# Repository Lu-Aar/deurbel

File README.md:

# deurbel
Making an ordinairy doorbell smart by having a notification through discord and ringing a klikaanklikuit chime.

When the doorbell is pressed there are three notifications:
- A mechanical chime
- A KlikAanKlikUit chime
- A Discord notification

There are also two extra inputs:
- A test button: Added to to test the doorbell functionality
- A mute switch: This can enable/disable the chimes

This project is fully designed in RUST no_std and it's designed to be used with a ESP32-WROOM-32.

## ToDo after clone
When this repo is cloned there is one step which has to be done before the code can be used.
Inside the bin folder the following file needs to be created:
global/mod.rs

This file should contain the following items:
``` rust
pub const WIFI_SSID: &str = "THE_SSID_TO_CONNECT_TO";
pub const WIFI_PASSWORD: &str = "THE_PASSWORD_OF_THE_SSID";
pub const DISCORD_WEBHOOK_URL: &str = "THE_URL_OF_THE_DISCORD_WEBHOOK_TO_USE";
pub const DISCORD_TTS: &str = false; // Set to true when to use Text To Speech
```

## PCB
The PCB was created in KiCad. It's a free opensource program for creating schematics and PCB's.
https://www.kicad.org/

## How to flash
. export-esp.sh

cargo build && cargo run

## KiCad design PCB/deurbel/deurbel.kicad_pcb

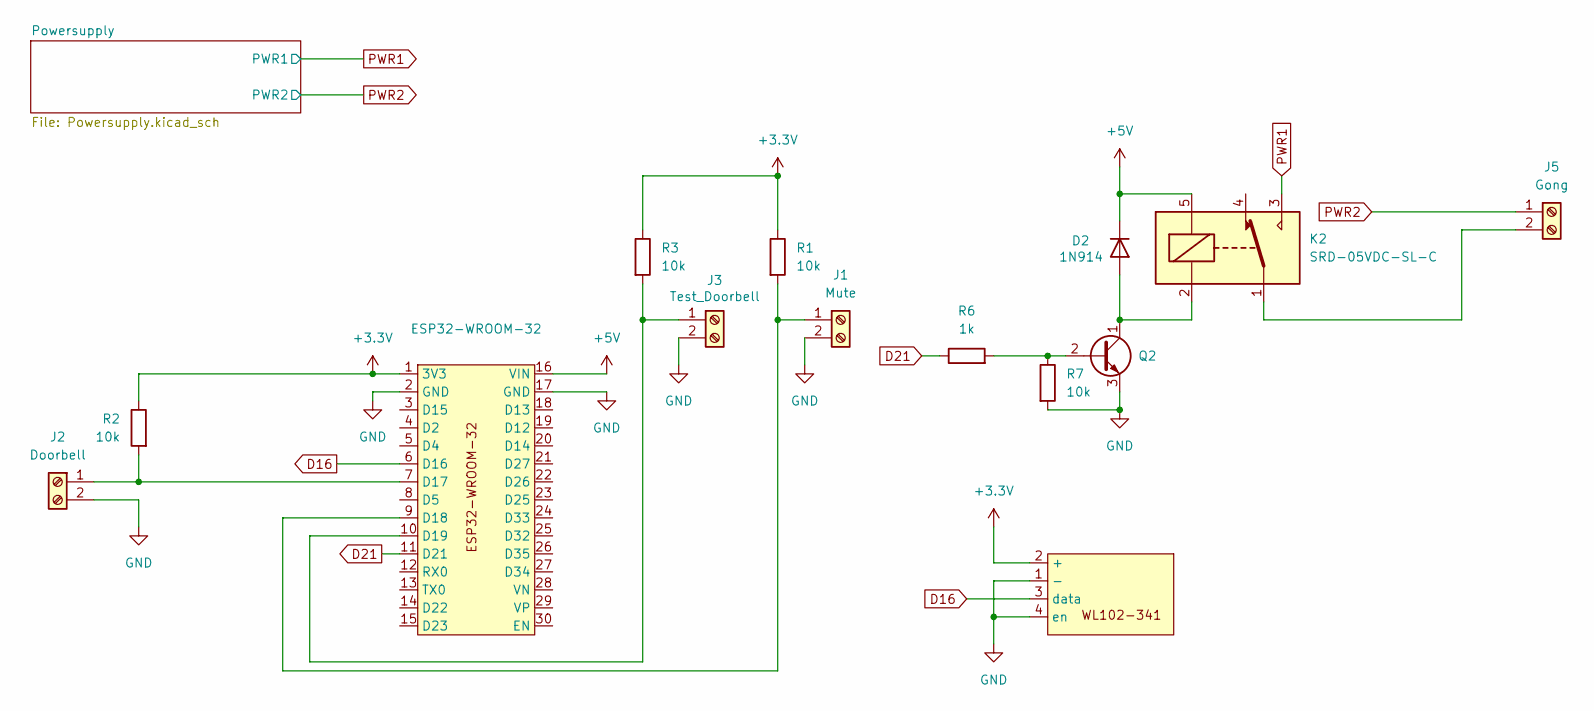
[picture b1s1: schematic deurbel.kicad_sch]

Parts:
D2: 1N914; D_DO-35_SOD27_P7.62mm_Horizontal
ESP32-WROOM-32: ESP32-WROOM-32
J1: Mute; TerminalBlock_Xinya_XY308-2.54-2P_1x02_P2.54mm_Horizontal
J2: Doorbell; TerminalBlock_Xinya_XY308-2.54-2P_1x02_P2.54mm_Horizontal
J3: Test_Doorbell; TerminalBlock_Xinya_XY308-2.54-2P_1x02_P2.54mm_Horizontal
J5: Gong; TerminalBlock_Xinya_XY308-2.54-2P_1x02_P2.54mm_Horizontal
K2: SRD-05VDC-SL-C; Relay_SPDT_SANYOU_SRD_Series_Form_C
Q2: BC338; TO-92_Inline
R1, R2, R3, R7: 10k; R_Axial_DIN0204_L3.6mm_D1.6mm_P5.08mm_Horizontal
R6: 1k; R_Axial_DIN0204_L3.6mm_D1.6mm_P5.08mm_Horizontal
WL102-1: WL102-341

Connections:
+3.3V: ESP32-WROOM-32.1 (3V3), R1.1, R2.1, R3.1, WL102-1.2 (+)
+5V: D2.1 (K), ESP32-WROOM-32.16 (VIN), K2.5; also elsewhere on the board
D16: ESP32-WROOM-32.6 (D16), WL102-1.3 (data)
D21: ESP32-WROOM-32.11 (D21), R6.1
GND: ESP32-WROOM-32.2 (GND), ESP32-WROOM-32.17 (GND), J1.2, J2.2, J3.2, Q2.3 (E), R7.2, WL102-1.1 (-), WL102-1.4 (en); also elsewhere on the board
unnamed: D2.2 (A), K2.2, Q2.1 (C)
unnamed: ESP32-WROOM-32.7 (D17), J2.1, R2.2
unnamed: ESP32-WROOM-32.9 (D18), J1.1, R1.2
unnamed: ESP32-WROOM-32.10 (D19), J3.1, R3.2
unnamed: J5.2, K2.1
unnamed: Q2.2 (B), R6.2, R7.1
PWR1: K2.3; also elsewhere on the board
PWR2: J5.1; also elsewhere on the board

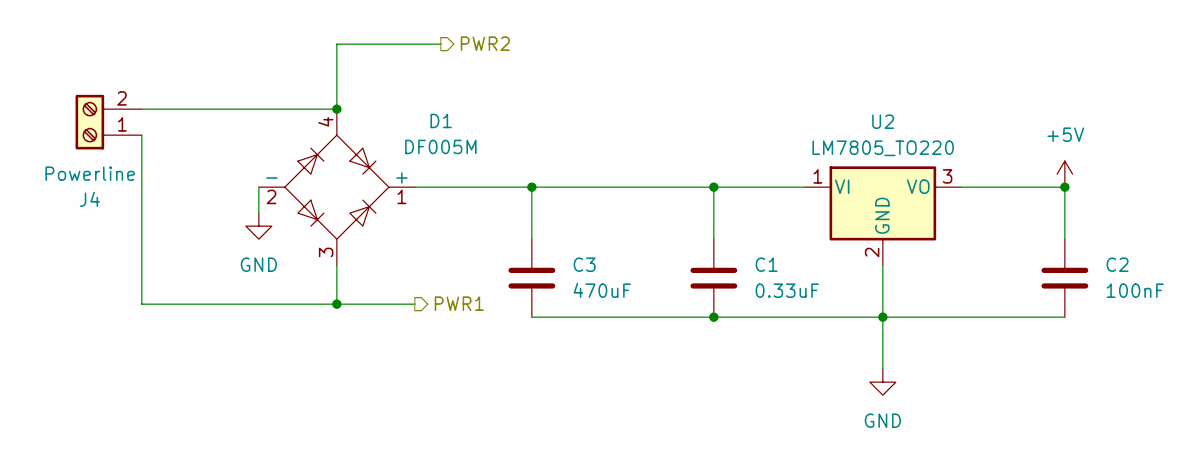
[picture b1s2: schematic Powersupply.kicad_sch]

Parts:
C1: 0.33uF; C_Disc_D4.3mm_W1.9mm_P5.00mm
C2: 100nF; C_Disc_D4.3mm_W1.9mm_P5.00mm
C3: 470uF; CP_Radial_D10.0mm_P5.00mm
D1: DF005M; Diode_Bridge_DIP-4_W7.62mm_P5.08mm
J4: Powerline; TerminalBlock_Xinya_XY308-2.54-2P_1x02_P2.54mm_Horizontal
U2: LM7805_TO220; TO-220-3_Vertical

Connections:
+5V: C2.1, U2.3 (VO); also elsewhere on the board
GND: C1.2, C2.2, C3.2, D1.2 (-), U2.2 (GND); also elsewhere on the board
unnamed: C1.1, C3.1, D1.1 (+), U2.1 (VI)
PWR1: D1.3, J4.1; also elsewhere on the board
PWR2: D1.4, J4.2; also elsewhere on the board

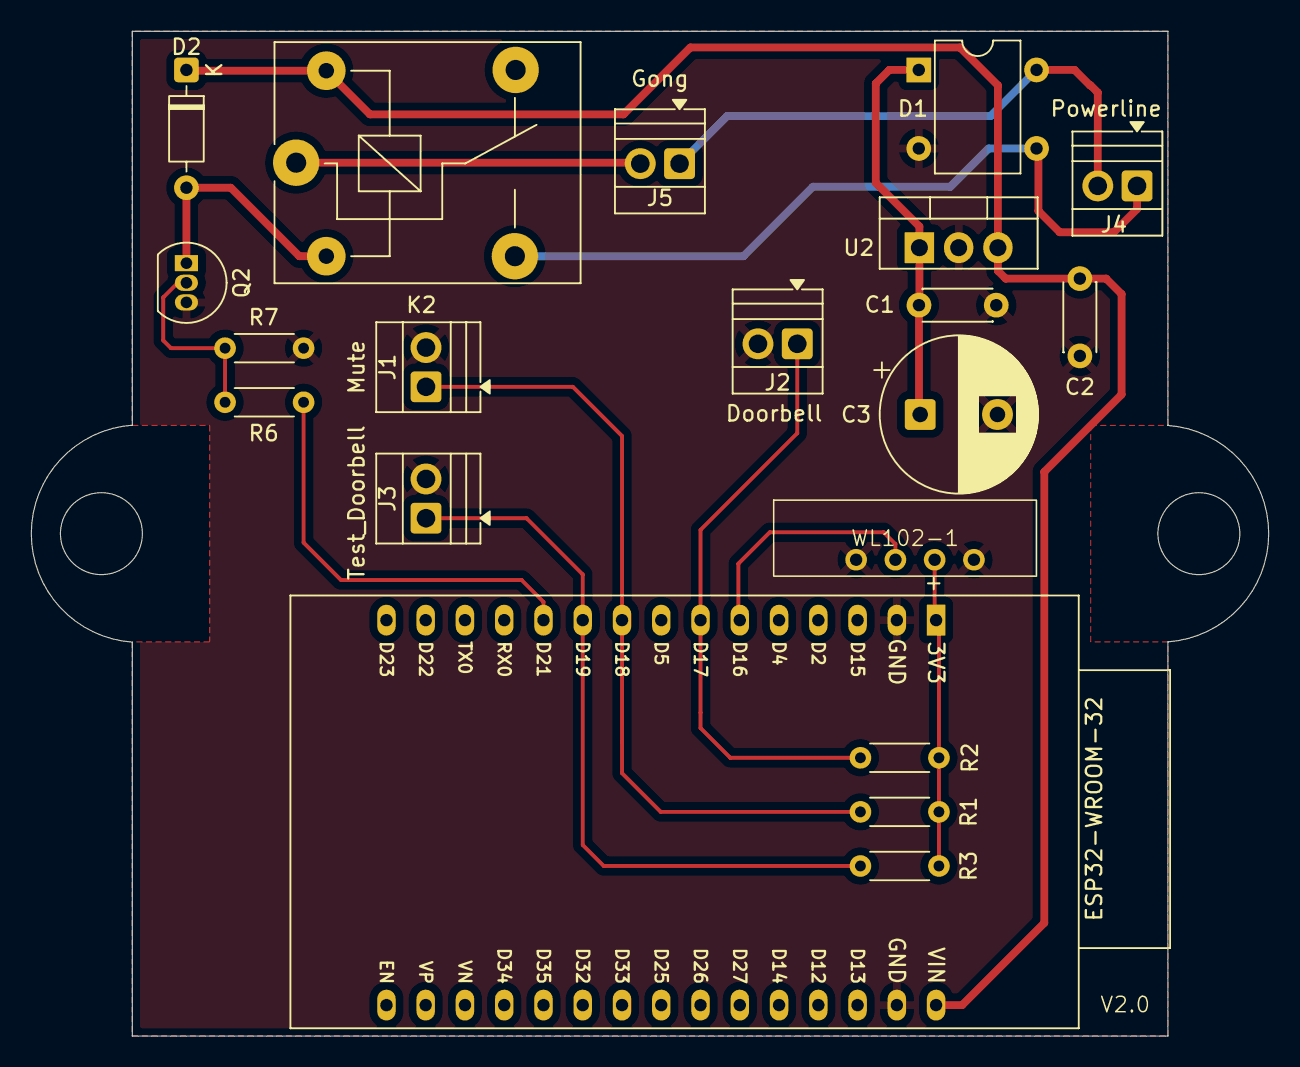
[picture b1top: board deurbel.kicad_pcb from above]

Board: 2 copper layers, 80.1 x 65.0 mm, 20 parts (0 on the bottom side), 14 nets.

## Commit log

2025-07-13 The ringing of the chime is working, started with Discord communication
2025-07-13 After a lot of struggle the ESP32 can connect to WiFi. The next step is to be able to send to discord
2025-07-13 Commented out what is currently broken
2025-07-16 Used the STD to send a message to discord and ring the chime
2025-07-24 After a lot of trying finally got it working. The readme of the crate was wrong. The functionality has been updated without updating the readme... Could've saved me a lot of headache in looking throu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
2025-07-24 Added the buttons to trigger the doorbell
2025-08-15 Created a struct to check pin state
2025-08-15 Created a PCB for the doorbell. It's designed to fit inside a junction box
2025-08-15 Updated the readme to give more info
2025-08-15 Removed unused functionality and included the physical chime. For now untested. If no update, it works
2026-03-03 Client config is now done once and removed scanning from connection task
2026-03-05 Made something to know if I am testing or somebody is at the door
2026-04-22 Fix flashing command in README.md
    Updated the flashing instructions in the README.
